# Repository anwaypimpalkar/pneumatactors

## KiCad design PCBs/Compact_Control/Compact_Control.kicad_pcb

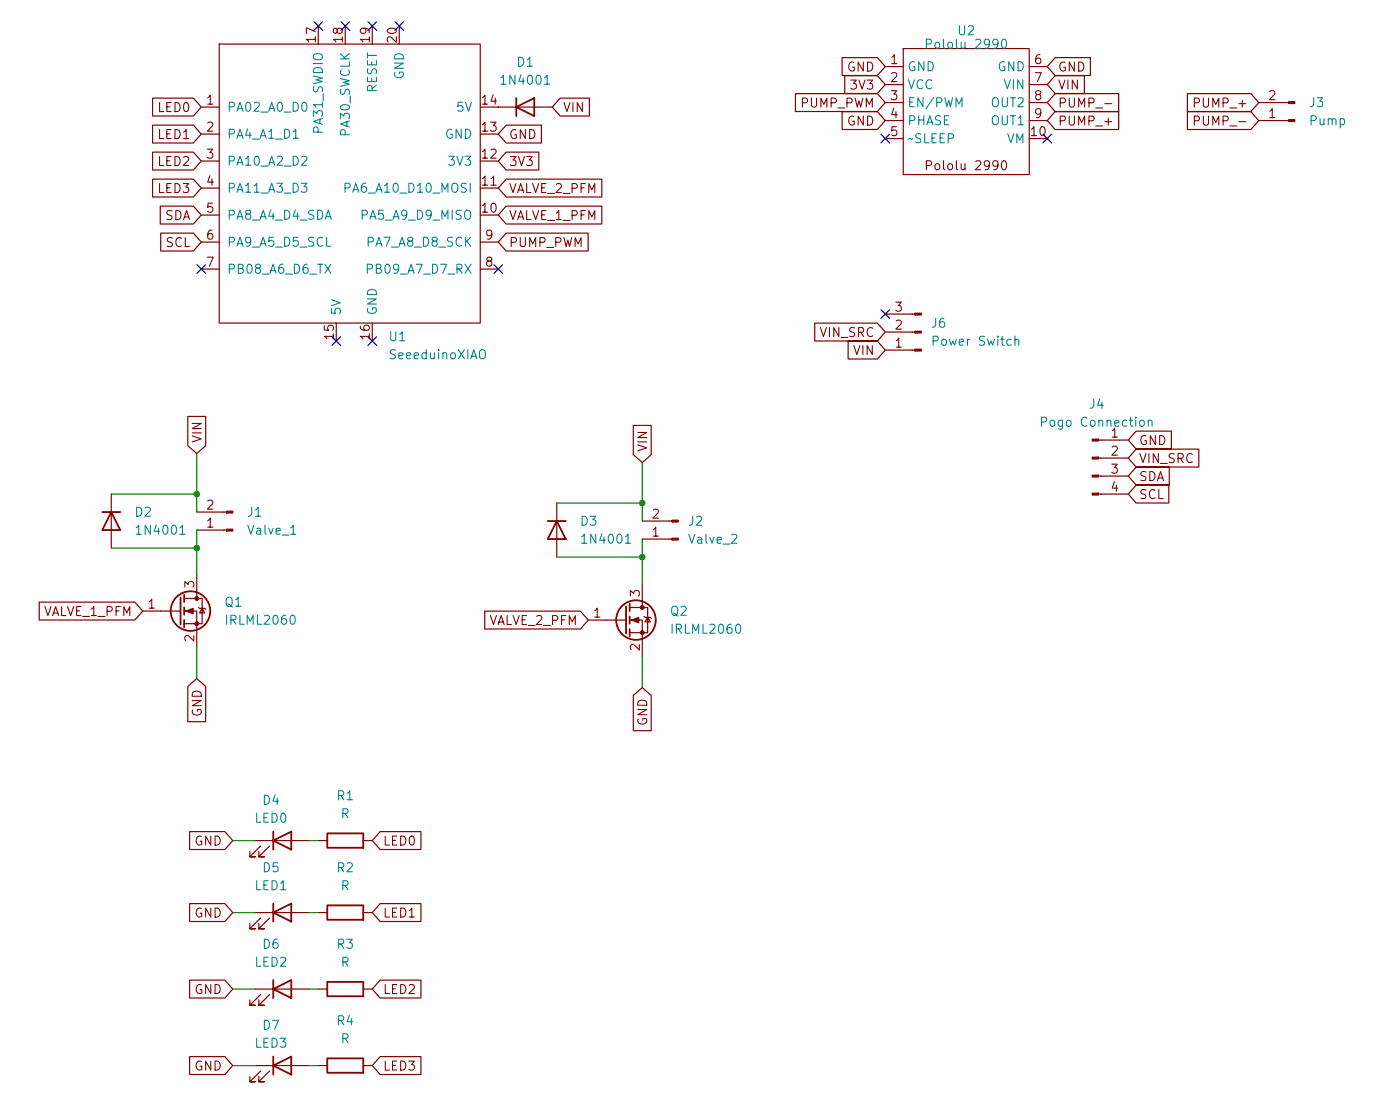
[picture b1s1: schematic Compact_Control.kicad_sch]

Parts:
D1, D2, D3: 1N4001; D_SOD-123F
D4: LED0; LED_0201_0603Metric_Pad0.64x0.40mm_HandSolder
D5: LED1; LED_0201_0603Metric_Pad0.64x0.40mm_HandSolder
D6: LED2; LED_0201_0603Metric_Pad0.64x0.40mm_HandSolder
D7: LED3; LED_0201_0603Metric_Pad0.64x0.40mm_HandSolder
J1: Valve_1; PinHeader_1x02_P2.54mm_Vertical
J2: Valve_2; PinHeader_1x02_P2.54mm_Vertical
J3: Pump; PinHeader_1x02_P2.54mm_Vertical
J4: Pogo Connection; PinHeader_1x04_P2.54mm_Vertical
J6: Power Switch; PinHeader_1x03_P2.54mm_Vertical
Q1, Q2: IRLML2060; SOT-23
R1, R2, R3, R4: R; R_0201_0603Metric_Pad0.64x0.40mm_HandSolder
U1: SeeeduinoXIAO; XIAO-Generic-Thruhole-14P-2.54-21X17.8MM
U2: Pololu 2990; Pololu 2990 Motor Driver

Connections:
3V3: U1.12 (3V3), U2.2 (VCC)
GND: D4.1 (K), D5.1 (K), D6.1 (K), D7.1 (K), J4.1, Q1.2 (S), Q2.2 (S), U1.13 (GND), U2.1 (GND), U2.4 (PHASE), U2.6 (GND)
LED0: R1.2, U1.1 (PA02_A0_D0)
LED1: R2.2, U1.2 (PA4_A1_D1)
LED2: R3.2, U1.3 (PA10_A2_D2)
LED3: R4.2, U1.4 (PA11_A3_D3)
unnamed: D1.1 (K), U1.14 (5V)
unnamed: D2.2 (A), J1.1, Q1.3 (D)
unnamed: D3.2 (A), J2.1, Q2.3 (D)
unnamed: D4.2 (A), R1.1
unnamed: D5.2 (A), R2.1
unnamed: D6.2 (A), R3.1
unnamed: D7.2 (A), R4.1
PUMP_+: J3.2, U2.9 (OUT1)
PUMP_-: J3.1, U2.8 (OUT2)
PUMP_PWM: U1.9 (PA7_A8_D8_SCK), U2.3 (EN/PWM)
SCL: J4.4, U1.6 (PA9_A5_D5_SCL)
SDA: J4.3, U1.5 (PA8_A4_D4_SDA)
VALVE_1_PFM: Q1.1 (G), U1.10 (PA5_A9_D9_MISO)
VALVE_2_PFM: Q2.1 (G), U1.11 (PA6_A10_D10_MOSI)
VIN: D1.2 (A), D2.1 (K), D3.1 (K), J1.2, J2.2, J6.1, U2.7 (VIN)
VIN_SRC: J4.2, J6.2

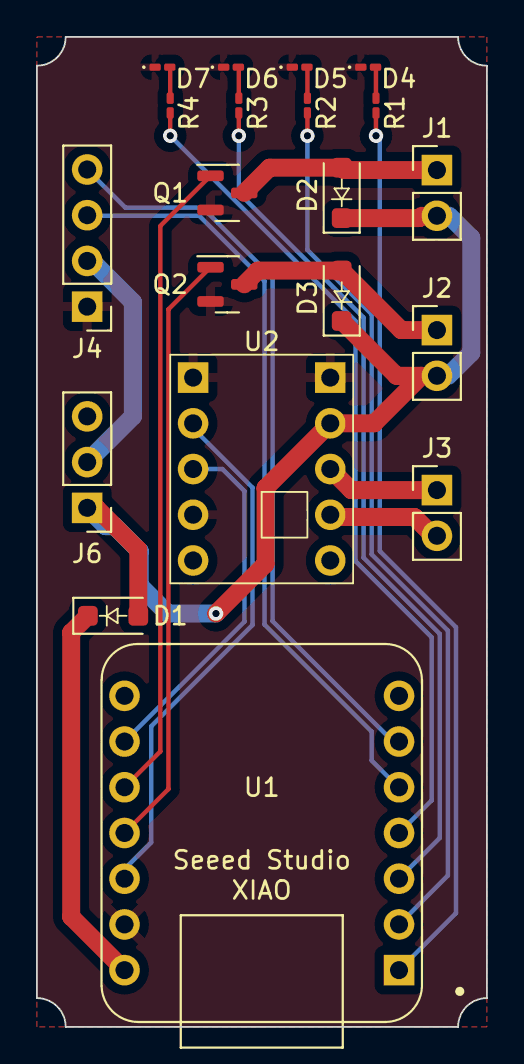
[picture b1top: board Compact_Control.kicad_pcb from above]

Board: 2 copper layers, 25.0 x 55.0 mm, 20 parts (0 on the bottom side), 22 nets.

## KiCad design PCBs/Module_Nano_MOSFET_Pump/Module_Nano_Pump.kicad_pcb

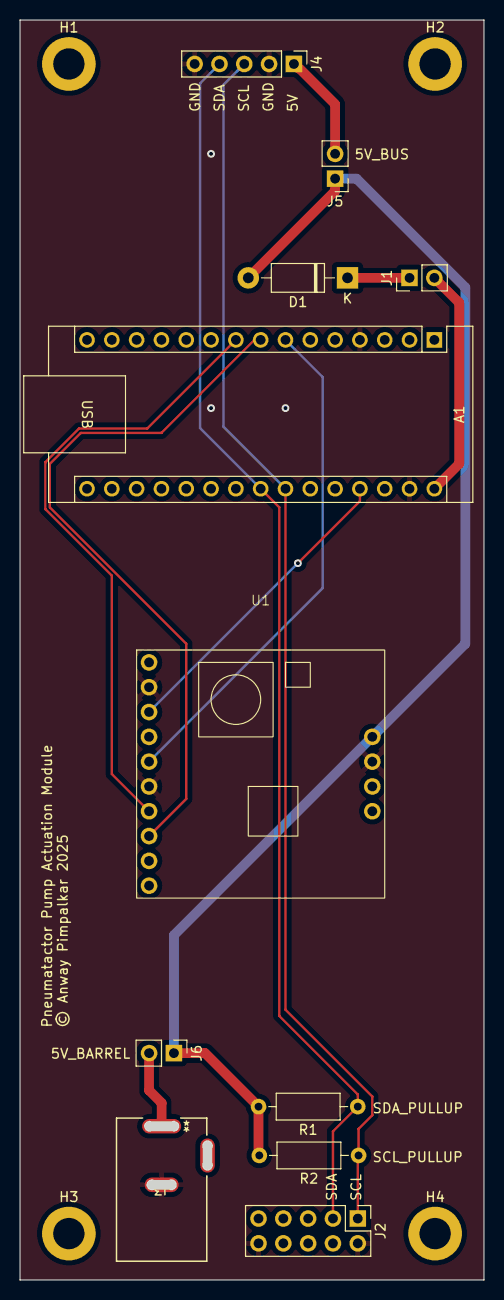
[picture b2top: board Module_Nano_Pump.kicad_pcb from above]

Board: 2 copper layers, 47.5 x 129.0 mm, 15 parts (0 on the bottom side), 12 nets.

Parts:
A1: Arduino_Nano_Every; Arduino_Nano
D1: 1N4001; D_DO-41_SOD81_P10.16mm_Horizontal
H1, H2, H3, H4: MountingHole; MountingHole_3.2mm_M3_ISO14580_Pad
J1, J5, J6: Conn_01x02_Pin; PinHeader_1x02_P2.54mm_Vertical
J2: Conn_02x05_Odd_Even; PinHeader_2x05_P2.54mm_Vertical
J3: PJ-002A; PJ-002A_CUD
J4: Conn_01x05_Pin; PinHeader_1x05_P2.54mm_Vertical
R1, R2: R; R_Axial_DIN0207_L6.3mm_D2.5mm_P10.16mm_Horizontal
U1: Pololu 2997 Motor Driver

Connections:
5V: D1.2 (A), J5.1, J6.1, R1.2, R2.2, U1.11 (VIN)
5V_BARREL: J3.1, J6.2
5V_BUS: J4.1, J5.2
5V_NANO: A1.27 (+5V), U1.3 (VCC)
EN: A1.7 (D4), U1.5 (EN)
GND: A1.4 (GND), A1.29 (GND), J2.2, J2.10, J3.2, J4.2, J4.5, U1.2 (GND), U1.6 (ENB), U1.12 (GND)
unnamed: A1.30 (VIN), J1.2
unnamed: D1.1 (K), J1.1
PWM1: A1.8 (D5), U1.8 (PWM1)
PWM2: A1.9 (D6), U1.7 (PWM2)
SCL: A1.24 (SCL/A5), J2.1, J4.3, R2.1
SDA: A1.23 (SDA/A4), J2.3, J4.4, R1.1

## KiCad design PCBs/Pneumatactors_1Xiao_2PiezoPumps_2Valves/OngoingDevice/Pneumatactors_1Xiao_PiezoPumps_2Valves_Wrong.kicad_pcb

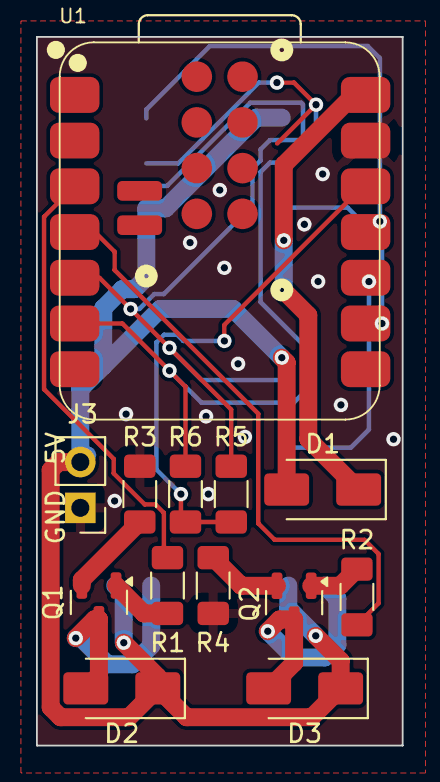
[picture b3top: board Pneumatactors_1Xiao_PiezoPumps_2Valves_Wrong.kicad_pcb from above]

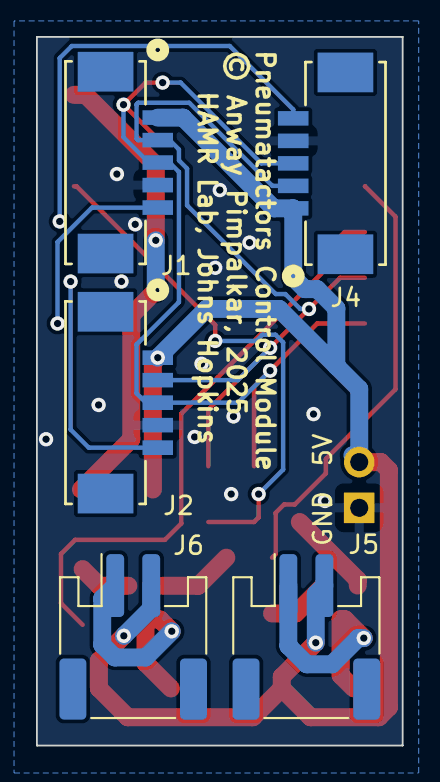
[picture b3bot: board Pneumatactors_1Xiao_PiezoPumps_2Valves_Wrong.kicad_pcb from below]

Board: 2 copper layers, 20.3 x 39.4 mm, 18 parts (5 on the bottom side), 17 nets.

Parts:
D1, D2, D3: 1N5819; D_SMA
J1, J2, J4: 532610571; CONN_532610001-SD_05_MOL
J3: Conn_01x02_Pin; PinHeader_1x02_P2.54mm_Vertical
J5: Valve_1; JST_PH_S2B-PH-SM4-TB_1x02-1MP_P2.00mm_Horizontal
J6: Valve_2; JST_PH_S2B-PH-SM4-TB_1x02-1MP_P2.00mm_Horizontal
Q1, Q2: IRLML2060; SOT-23
R1, R2: 220; R_1206_3216Metric_Pad1.30x1.75mm_HandSolder
R3, R4, R5, R6: 10k; R_1206_3216Metric_Pad1.30x1.75mm_HandSolder
U1: SeeeduinoXIAO; XIAO-ESP32S3-SMD

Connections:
3V3: R5.2, R6.2, U1.12 (3V3)
5V: D1.2 (A), D2.1 (K), D3.1 (K), J1.1, J2.1, J3.2, J4.1, J5.2, J6.2
GND: J1.4, J2.4, J3.1, J4.4, R3.2, R4.2, U1.13 (GND)
unnamed: D1.1 (K), U1.14 (5V)
unnamed: D2.2 (A), J5.1, Q1.3 (D)
unnamed: D3.2 (A), J6.1, Q2.3 (D)
unnamed: Q1.1 (G), R1.2
unnamed: Q1.2 (S), R3.1
unnamed: Q2.1 (G), R2.2
unnamed: Q2.2 (S), R4.1
P1_A: J1.5, U1.9 (PA7_A8_D8_SCK)
P2_A: J2.5, U1.10 (PA5_A9_D9_MISO)
P3_A: J4.5, U1.11 (PA6_A10_D10_MOSI)
SCL: J1.3, J2.3, J4.3, R6.1, U1.6 (PA9_A5_D5_SCL)
SDA: J1.2, J2.2, J4.2, R5.1, U1.5 (PA8_A4_D4_SDA)
V1: R1.1, U1.3 (PA10_A2_D2)
V2: R2.1, U1.4 (PA11_A3_D3)

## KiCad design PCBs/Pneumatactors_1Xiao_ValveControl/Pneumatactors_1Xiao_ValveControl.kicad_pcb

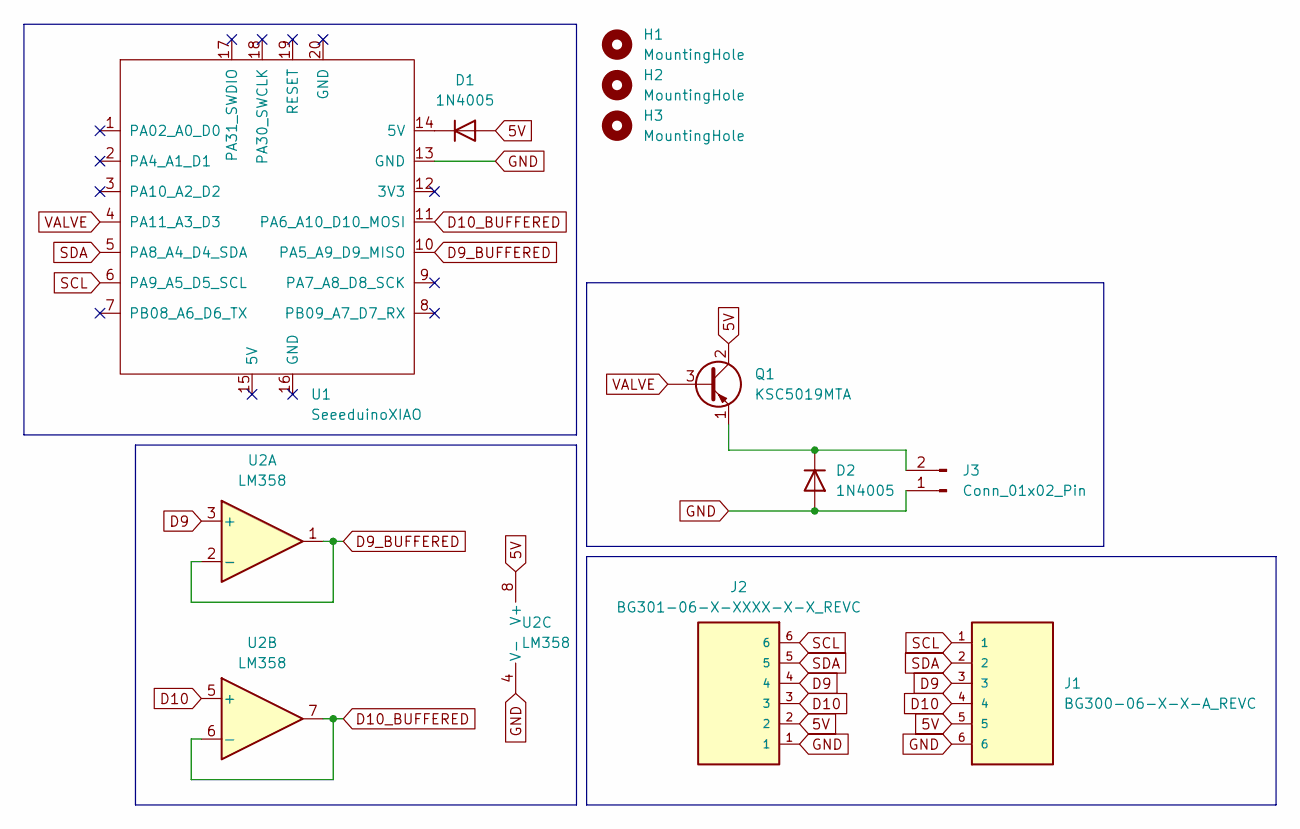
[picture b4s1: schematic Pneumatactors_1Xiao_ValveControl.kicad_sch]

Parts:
D1, D2: 1N4005; D_DO-41_SOD81_P10.16mm_Horizontal
H1, H2, H3: MountingHole; MountingHole_2.2mm_M2_ISO14580
J1: BG300-06-X-X-A_REVC; GCT_BG300-06-X-X-A_REVC
J2: BG301-06-X-XXXX-X-X_REVC; GCT_BG301-06-X-XXXX-X-X_REVC
J3: Conn_01x02_Pin; PinHeader_1x02_P2.54mm_Vertical
Q1: KSC5019MTA; TO-92L_Inline_Wide
U1: SeeeduinoXIAO; XIAO-Generic-Thruhole-14P-2.54-21X17.8MM
U2: LM358; SOIC_58BAIDR_TEX_LM358

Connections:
5V: D1.2 (A), J1.5, J2.2, Q1.2 (C), U2.8 (V+)
D9: J1.3, J2.4, U2.3 (+)
D9_BUFFERED: U1.10 (PA5_A9_D9_MISO), U2.1, U2.2 (-)
D10: J1.4, J2.3, U2.5 (+)
D10_BUFFERED: U1.11 (PA6_A10_D10_MOSI), U2.6 (-), U2.7
GND: D2.2 (A), J1.6, J2.1, J3.1, U1.13 (GND), U2.4 (V-)
unnamed: D1.1 (K), U1.14 (5V)
unnamed: D2.1 (K), J3.2, Q1.1 (E)
SCL: J1.1, J2.6, U1.6 (PA9_A5_D5_SCL)
SDA: J1.2, J2.5, U1.5 (PA8_A4_D4_SDA)
VALVE: Q1.3 (B), U1.4 (PA11_A3_D3)

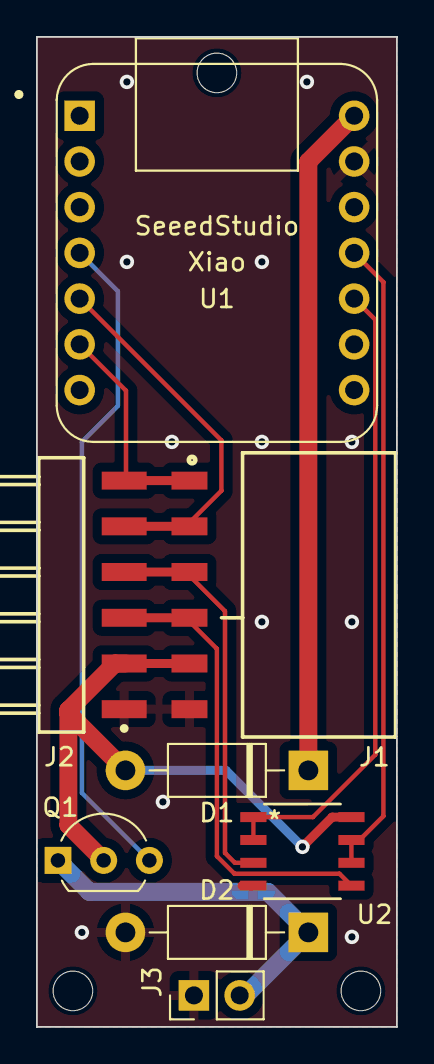
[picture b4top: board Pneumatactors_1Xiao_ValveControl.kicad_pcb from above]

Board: 2 copper layers, 20.0 x 55.0 mm, 11 parts (0 on the bottom side), 11 nets.

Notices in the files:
PCBs/Compact_Control/Compact_Control.kicad_pcb:
© Anway Pimpalkar 2025
PCBs/Pneumatactors_1Xiao_ValveControl/Pneumatactors_1Xiao_ValveControl.kicad_pcb:
© A. Pimpalkar, HAMR Lab 2024
